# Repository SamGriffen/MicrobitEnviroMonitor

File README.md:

# MicrobitEnviroMonitor
ESP based webserver for displaying data from weather:bit. This project will allow for the sparkfun weather:bit to send data to an ESP32, which will then display the data on a local webpage. The ESP32 must have a network to connect to, it does not create it's own local access point.

# MicroBit Code
MicroBit code can be downloaded here: https://makecode.microbit.org/_66RTrKJwsf48
The hex file can be found in the `microbit` folder of the repository.
 
 # Setup
 After cloning the repository, the project can be opened in PlatformIO. Web data is loaded into the SPIFFs storage on the ESP32, and the platformio config files are setup to allow for this. To install out of the box you must do the following:
 
 - Edit `ssid` and `password` at the top of the file to contain your WiFi network credentials.
 - Plug in ESP32.
 - From terminal, run `pio run --target uploadfs` in the root directory of the project. This will upload all web files to the ESP.
 - The project can then be uploaded as per usual.
 - Once running, the IP address of the ESP should be logged to the serial monitor (If DEBUG is defined). Navigate to this in a web browser, and the interface should appear.
 
 # Wiring Notes
 The following connections need to be made:
 weather:bit RX --> ESP32 GPIO17
 weather:bit TX --> ESP32 GPIO16
 weather:bit GND --> ESP32 GND

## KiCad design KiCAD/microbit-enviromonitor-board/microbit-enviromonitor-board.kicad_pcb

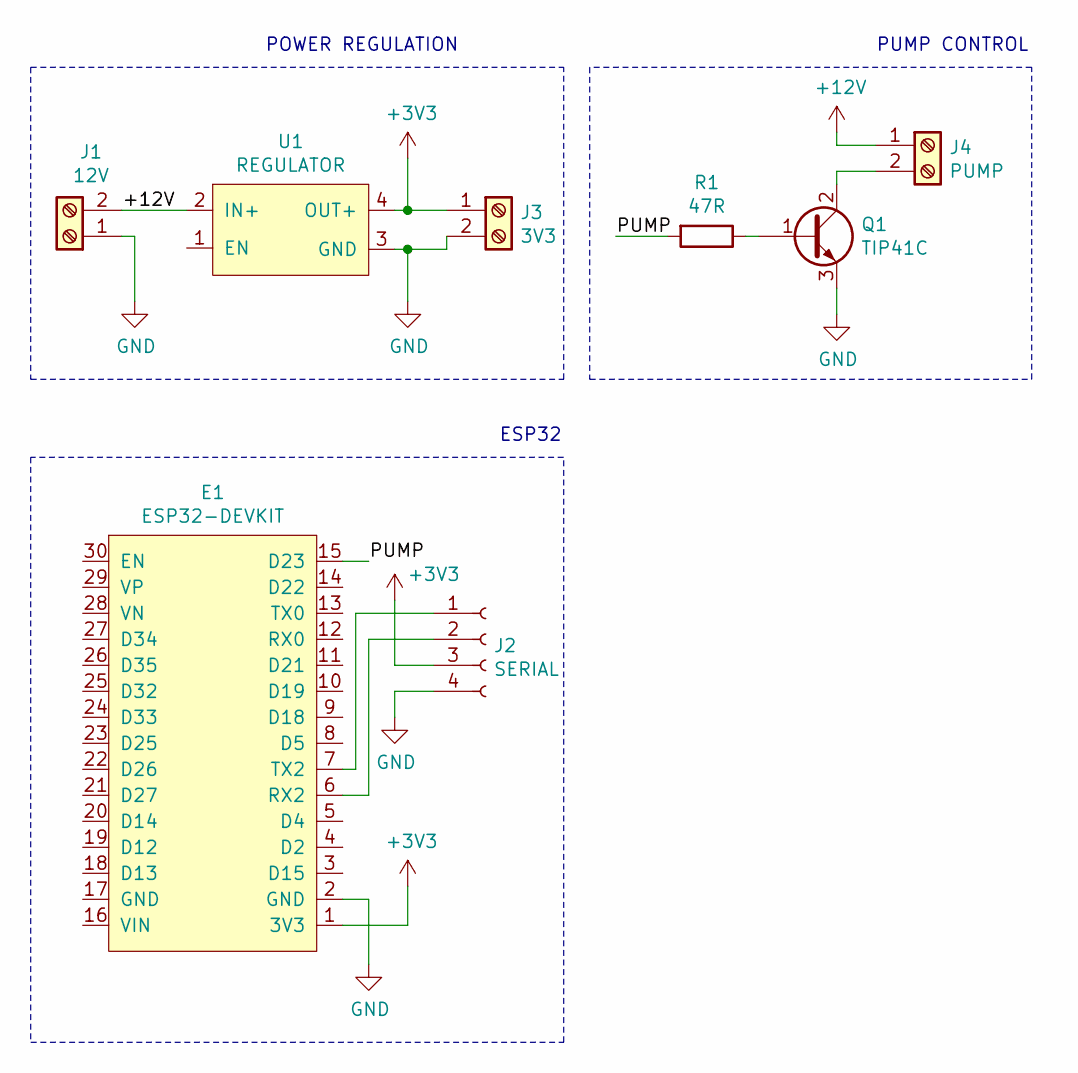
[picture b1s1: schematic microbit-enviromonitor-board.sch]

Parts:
E1: ESP32-DEVKIT; ESP31-DEVKIT
J1: 12V; screw_terminal
J2: SERIAL; 4x1
J3: 3V3; screw_terminal
J4: PUMP; screw_terminal
Q1: TIP41C; TO-220-3_Horizontal_TabDown
R1: 47R; R_Axial_DIN0204_L3.6mm_D1.6mm_P7.62mm_Horizontal
U1: REGULATOR; buck_converter

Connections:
+3V3: E1.1 (3V3), J2.3, J3.1, U1.4 (OUT+)
+12V: J1.2, J4.1, U1.2 (IN+)
/PUMP: E1.15 (D23), R1.2
GND: E1.2 (GND), J1.1, J2.4, J3.2, Q1.3 (E), U1.3 (GND)
unnamed: E1.6 (RX2), J2.2
unnamed: E1.7 (TX2), J2.1
unnamed: J4.2, Q1.2 (C)
unnamed: Q1.1 (B), R1.1

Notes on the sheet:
POWER REGULATION
PUMP CONTROL
ESP32

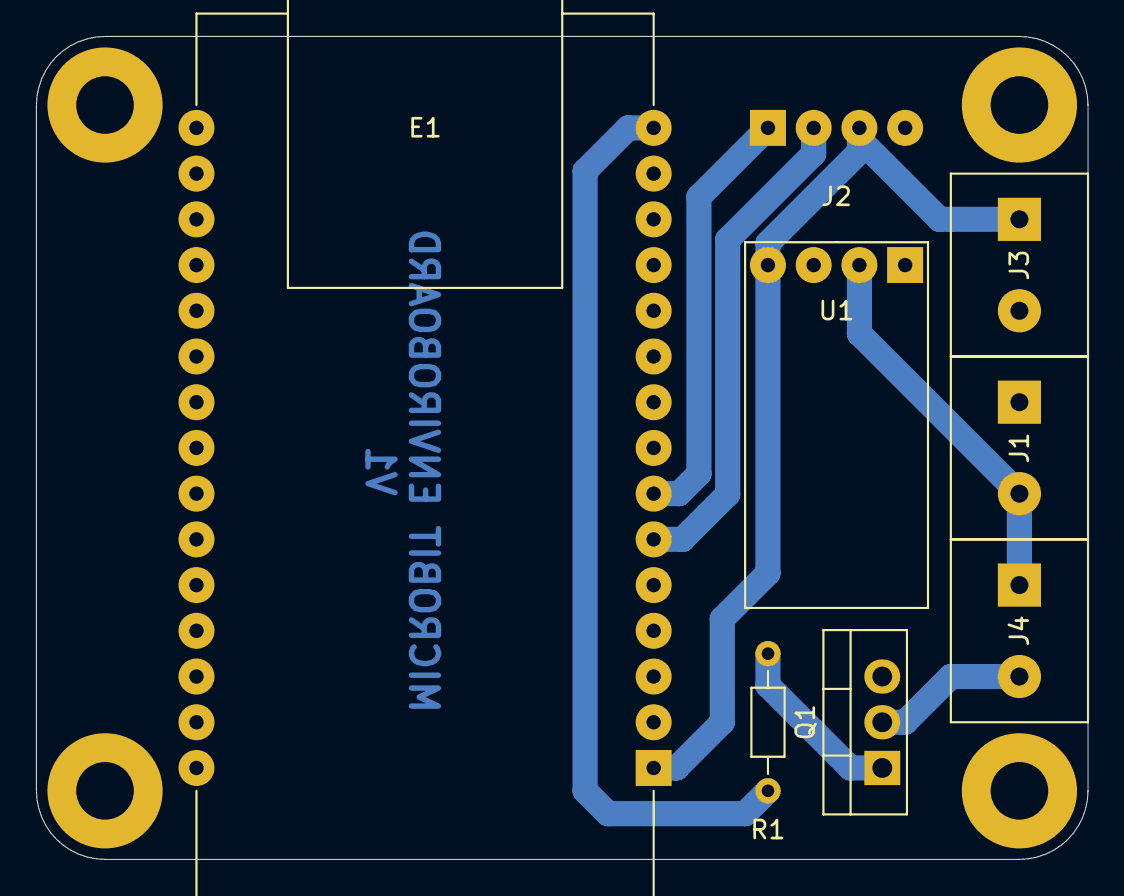
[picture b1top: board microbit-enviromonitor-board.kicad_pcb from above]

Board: 2 copper layers, 58.4 x 45.7 mm, 8 parts (0 on the bottom side), 8 nets.

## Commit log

2020-03-04 Increased soil moisture print accurracy
2020-03-08 CSS Tweaks
    Improved CSS, will now allow for soil moisture and pump status to be shown. Also made a unique soil moisture icon. Next step is to get these populating with actual controller data.
2020-03-09 Added pump state data
2020-03-14 Added wind data
2020-03-16 Modified pump control
2020-07-14 Began work on PCB
2020-07-17 Updated serial port
2020-07-17 Added exports
2020-07-19 Board changes
2020-08-19 Added pump switch
